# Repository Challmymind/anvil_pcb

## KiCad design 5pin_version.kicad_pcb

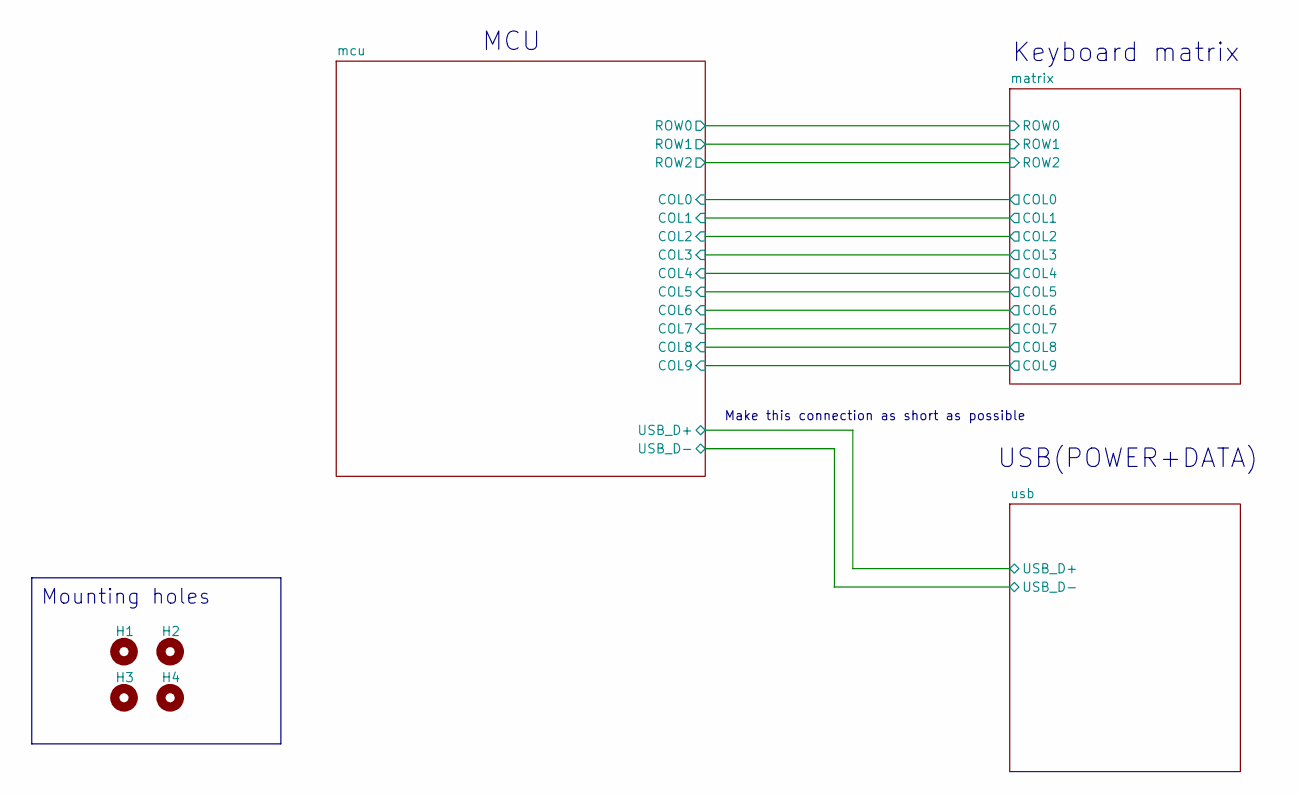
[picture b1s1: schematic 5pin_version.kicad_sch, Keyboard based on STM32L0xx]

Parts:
H1, H2, H3, H4: MountingHole; MountingHole_2.1mm

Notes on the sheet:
MCU
Keyboard matrix
Make this connection as short as possible
Mounting holes
USB(POWER+DATA)

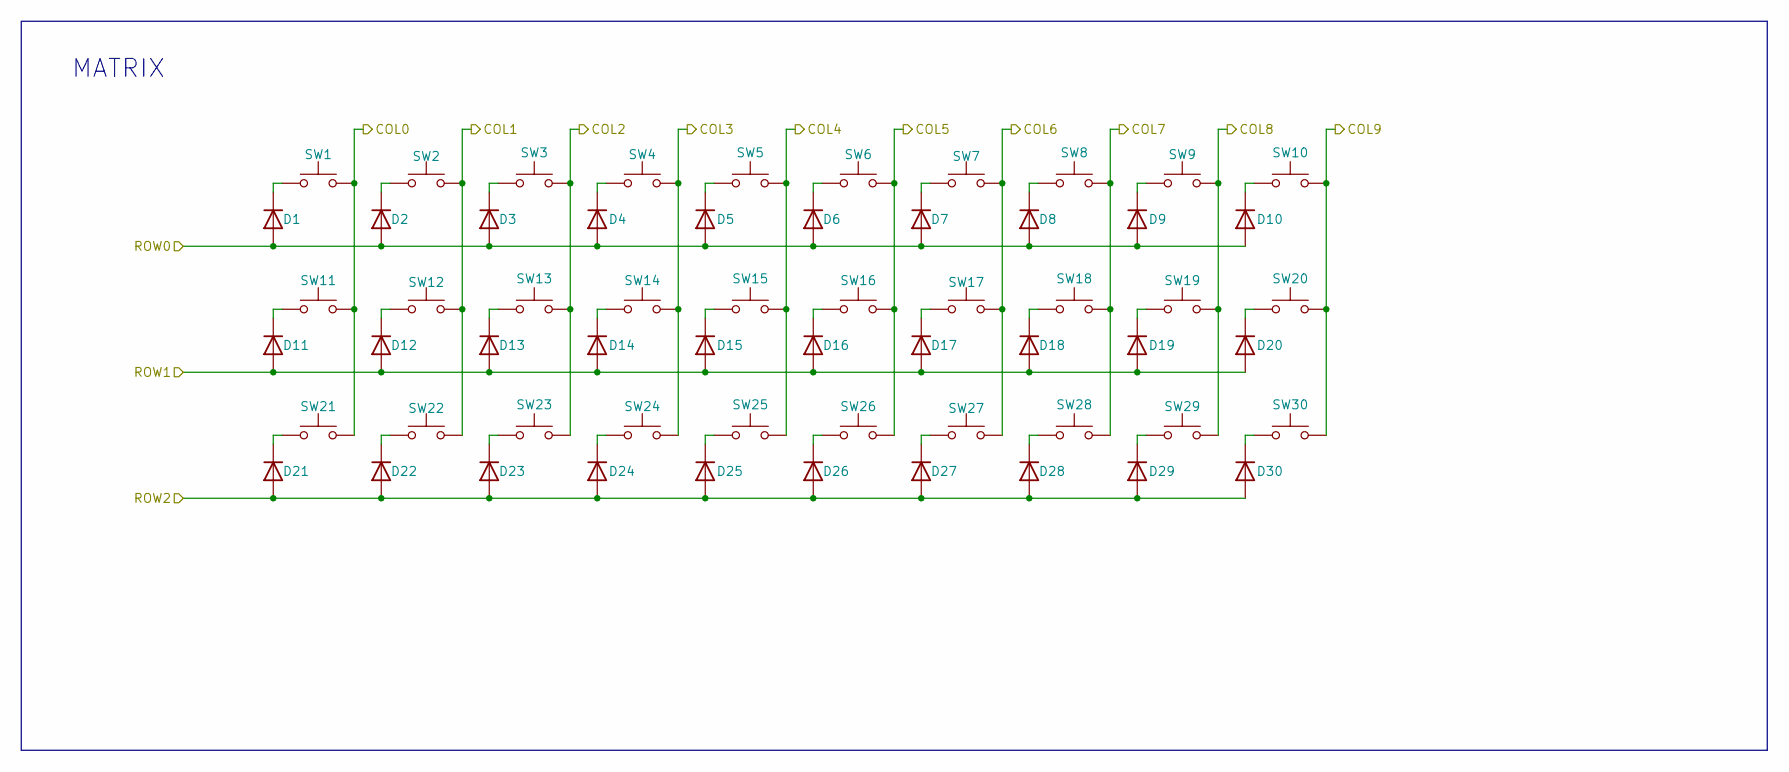
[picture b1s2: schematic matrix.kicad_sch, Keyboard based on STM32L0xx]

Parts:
D1, D2, D3, D4, D5, D6, D7, D8, D9, D10, D11, D12, D13, D14, D15, D16, D17, D18, D19, D20, D21, D22, D23, D24, D25, D26, D27, D28, D29, D30: D; D_SOD-123
SW1, SW2, SW3, SW4, SW5, SW6, SW7, SW8, SW9, SW10, SW11, SW12, SW13, SW14, SW15, SW16, SW17, SW18, SW19, SW20, SW21, SW22, SW23, SW24, SW25, SW26, SW27, SW28, SW29, SW30: SW_Push; SW_Cherry_MX_1.00u_PCB

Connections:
/matrix/COL0: SW1.2, SW11.2, SW21.2; also elsewhere on the board
/matrix/COL1: SW2.2, SW12.2, SW22.2; also elsewhere on the board
/matrix/COL2: SW3.2, SW13.2, SW23.2; also elsewhere on the board
/matrix/COL3: SW4.2, SW14.2, SW24.2; also elsewhere on the board
/matrix/COL4: SW5.2, SW15.2, SW25.2; also elsewhere on the board
/matrix/COL5: SW6.2, SW16.2, SW26.2; also elsewhere on the board
/matrix/COL6: SW7.2, SW17.2, SW27.2; also elsewhere on the board
/matrix/COL7: SW8.2, SW18.2, SW28.2; also elsewhere on the board
/matrix/COL8: SW9.2, SW19.2, SW29.2; also elsewhere on the board
/matrix/COL9: SW10.2, SW20.2, SW30.2; also elsewhere on the board
/matrix/ROW0: D1.2 (A), D2.2 (A), D3.2 (A), D4.2 (A), D5.2 (A), D6.2 (A), D7.2 (A), D8.2 (A), D9.2 (A), D10.2 (A); also elsewhere on the board
/matrix/ROW1: D11.2 (A), D12.2 (A), D13.2 (A), D14.2 (A), D15.2 (A), D16.2 (A), D17.2 (A), D18.2 (A), D19.2 (A), D20.2 (A); also elsewhere on the board
/matrix/ROW2: D21.2 (A), D22.2 (A), D23.2 (A), D24.2 (A), D25.2 (A), D26.2 (A), D27.2 (A), D28.2 (A), D29.2 (A), D30.2 (A); also elsewhere on the board
unnamed: D1.1 (K), SW1.1
unnamed: D2.1 (K), SW2.1
unnamed: D3.1 (K), SW3.1
unnamed: D4.1 (K), SW4.1
unnamed: D5.1 (K), SW5.1
unnamed: D6.1 (K), SW6.1
unnamed: D7.1 (K), SW7.1
unnamed: D8.1 (K), SW8.1
unnamed: D9.1 (K), SW9.1
unnamed: D10.1 (K), SW10.1
unnamed: D11.1 (K), SW11.1
unnamed: D12.1 (K), SW12.1
unnamed: D13.1 (K), SW13.1
unnamed: D14.1 (K), SW14.1
unnamed: D15.1 (K), SW15.1
unnamed: D16.1 (K), SW16.1
unnamed: D17.1 (K), SW17.1
unnamed: D18.1 (K), SW18.1
unnamed: D19.1 (K), SW19.1
unnamed: D20.1 (K), SW20.1
unnamed: D21.1 (K), SW21.1
unnamed: D22.1 (K), SW22.1
unnamed: D23.1 (K), SW23.1
unnamed: D24.1 (K), SW24.1
unnamed: D25.1 (K), SW25.1
unnamed: D26.1 (K), SW26.1
unnamed: D27.1 (K), SW27.1
unnamed: D28.1 (K), SW28.1
unnamed: D29.1 (K), SW29.1
unnamed: D30.1 (K), SW30.1

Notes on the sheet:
MATRIX

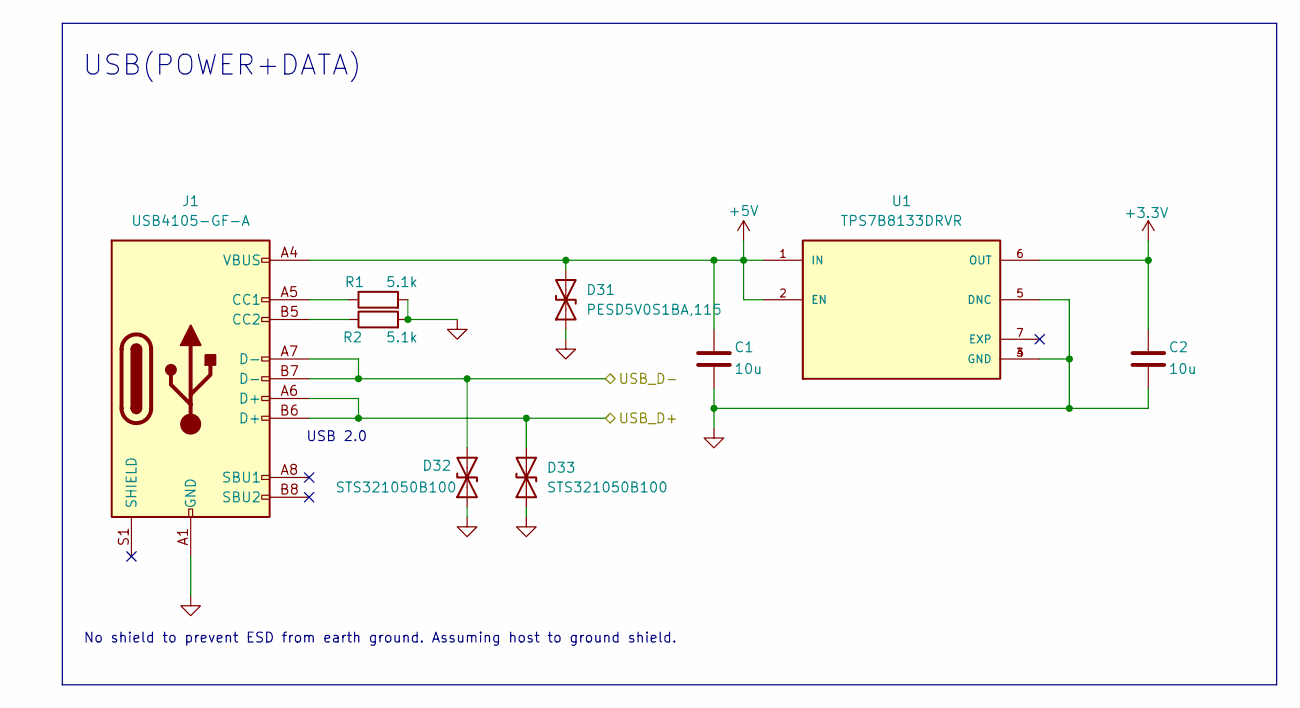
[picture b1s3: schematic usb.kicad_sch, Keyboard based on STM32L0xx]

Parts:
C1, C2: 10u; C_0603_1608Metric
D31: PESD5V0S1BA,115; D_SOD-323F
D32, D33: STS321050B100; D_SOD-323F
J1: USB4105-GF-A; USB_C_Receptacle_GCT_USB4105-xx-A_16P_TopMnt_Horizontal
R1, R2: 5.1k; R_0603_1608Metric
U1: TPS7B8133DRVR; SON65P200X200X80-7N; PARTREV April 2020

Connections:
+3.3V: C2.1, U1.6 (OUT); also elsewhere on the board
+5V: C1.1, D31.2 (A2), J1.A4 (VBUS), J1.A9 (VBUS), J1.B4 (VBUS), J1.B9 (VBUS), U1.1 (IN), U1.2 (EN)
/mcu/USB_D+: D33.2 (A2), J1.A6 (D+), J1.B6 (D+); also elsewhere on the board
/mcu/USB_D-: D32.2 (A2), J1.A7 (D-), J1.B7 (D-); also elsewhere on the board
GND: C1.2, C2.2, D31.1 (A1), D32.1 (A1), D33.1 (A1), J1.A1 (GND), J1.A12 (GND), J1.B1 (GND), J1.B12 (GND), R1.2, R2.2, U1.3 (GND), U1.4 (GND), U1.5 (DNC); also elsewhere on the board
unnamed: J1.A5 (CC1), R1.1
unnamed: J1.B5 (CC2), R2.1

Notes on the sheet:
USB(POWER+DATA)
USB 2.0
No shield to prevent ESD from earth ground. Assuming host to ground shield.

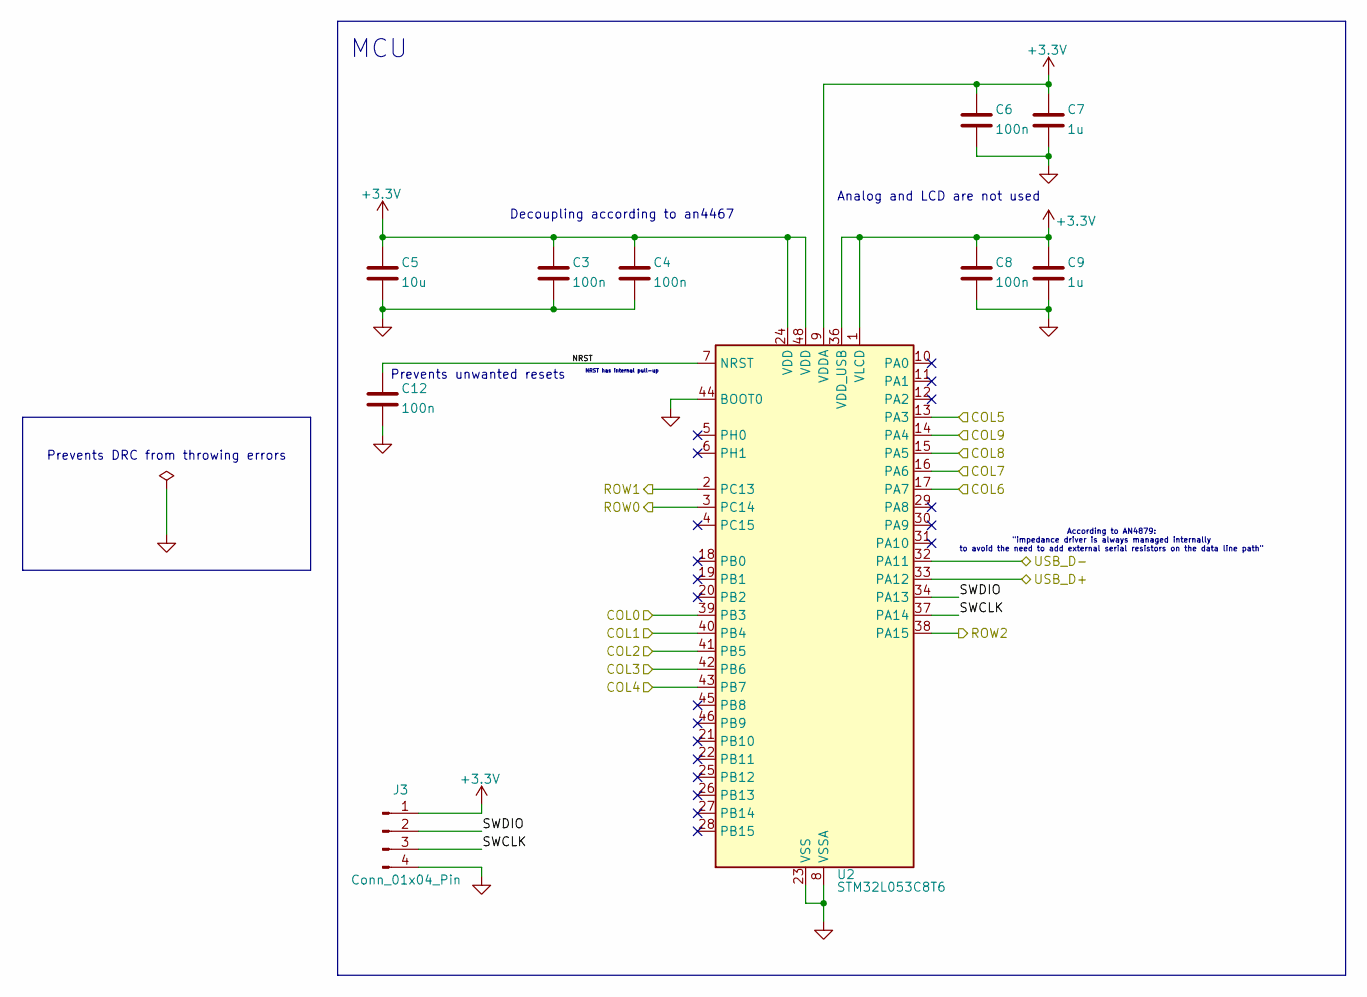
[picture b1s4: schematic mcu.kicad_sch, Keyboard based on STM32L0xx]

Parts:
C3, C4, C6, C8, C12: 100n; C_0603_1608Metric
C5: 10u; C_0603_1608Metric
C7, C9: 1u; C_0603_1608Metric
J3: Conn_01x04_Pin; PinHeader_1x04_P2.54mm_Vertical
U2: STM32L053C8T6; LQFP-48_7x7mm_P0.5mm

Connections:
+3.3V: C3.1, C4.1, C5.1, C6.1, C7.1, C8.1, C9.1, J3.1, U2.1 (VLCD), U2.9 (VDDA), U2.24 (VDD), U2.36 (VDD_USB), U2.48 (VDD); also elsewhere on the board
/matrix/COL0: U2.39 (PB3); also elsewhere on the board
/matrix/COL1: U2.40 (PB4); also elsewhere on the board
/matrix/COL2: U2.41 (PB5); also elsewhere on the board
/matrix/COL3: U2.42 (PB6); also elsewhere on the board
/matrix/COL4: U2.43 (PB7); also elsewhere on the board
/matrix/COL5: U2.13 (PA3); also elsewhere on the board
/matrix/COL6: U2.17 (PA7); also elsewhere on the board
/matrix/COL7: U2.16 (PA6); also elsewhere on the board
/matrix/COL8: U2.15 (PA5); also elsewhere on the board
/matrix/COL9: U2.14 (PA4); also elsewhere on the board
/matrix/ROW0: U2.3 (PC14); also elsewhere on the board
/matrix/ROW1: U2.2 (PC13); also elsewhere on the board
/matrix/ROW2: U2.38 (PA15); also elsewhere on the board
/mcu/NRST: C12.1, U2.7 (NRST)
/mcu/SWCLK: J3.3, U2.37 (PA14)
/mcu/SWDIO: J3.2, U2.34 (PA13)
/mcu/USB_D+: U2.33 (PA12); also elsewhere on the board
/mcu/USB_D-: U2.32 (PA11); also elsewhere on the board
GND: C3.2, C4.2, C5.2, C6.2, C7.2, C8.2, C9.2, C12.2, J3.4, U2.8 (VSSA), U2.23 (VSS), U2.35 (VSS), U2.44 (BOOT0), U2.47 (VSS); also elsewhere on the board

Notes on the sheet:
Decoupling according to an4467
Analog and LCD are not used
Prevents unwanted resets
Prevents DRC from throwing errors
According to AN4879: "impedance driver is always managed internally to avoid the need to add external serial resistors on the data line path"
NRST has internal pull-up
MCU

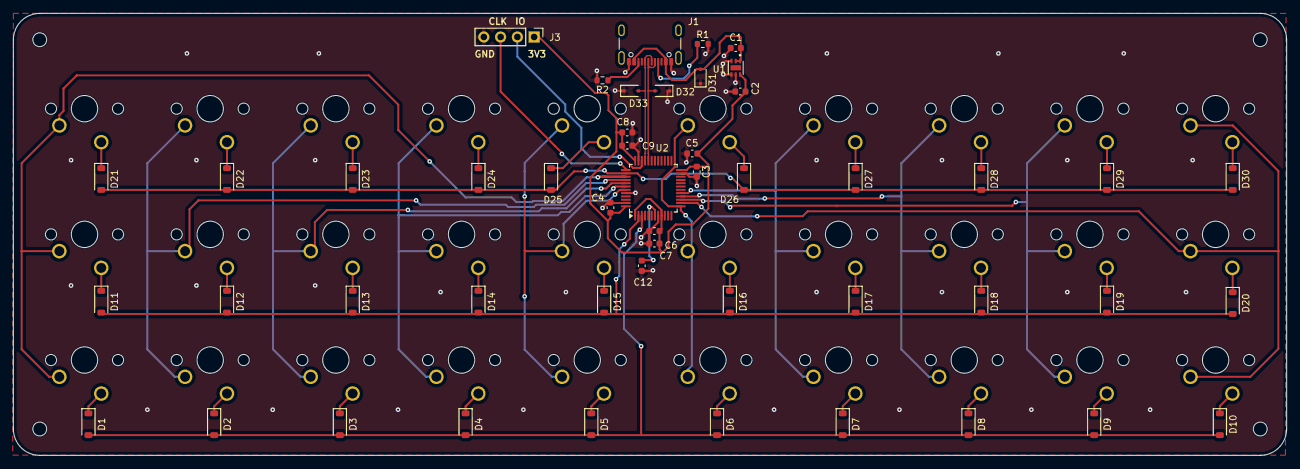
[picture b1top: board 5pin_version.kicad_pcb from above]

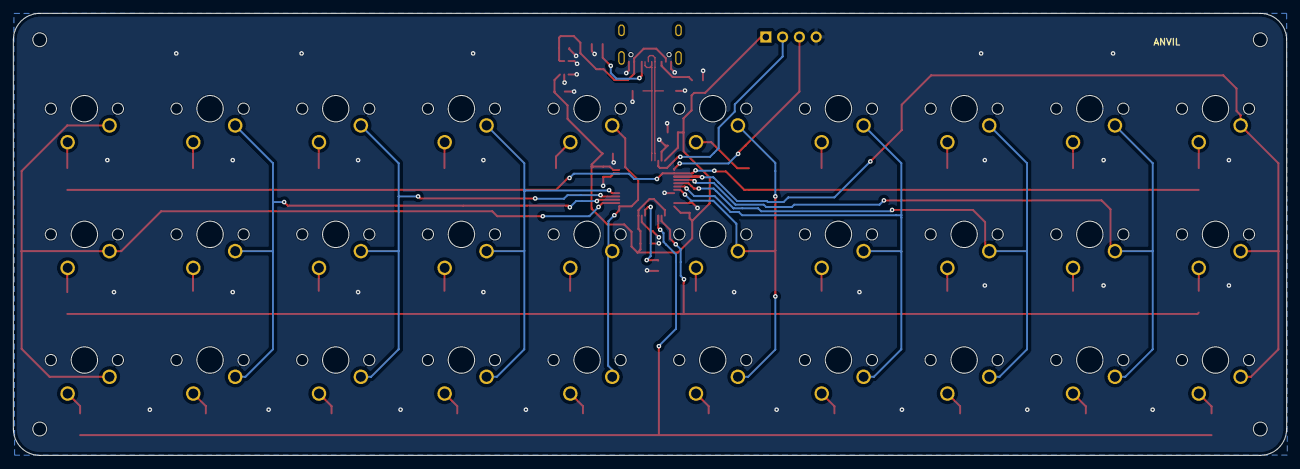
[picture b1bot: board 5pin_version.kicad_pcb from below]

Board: 2 copper layers, 193.0 x 67.0 mm, 83 parts (30 on the bottom side), 53 nets.

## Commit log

2024-07-04 first fixes (board size and switch layout)
2024-07-12 rewired most lines, changed sizes to make easier to solder
2024-07-14 completed re-routing
2024-07-16 board completed
